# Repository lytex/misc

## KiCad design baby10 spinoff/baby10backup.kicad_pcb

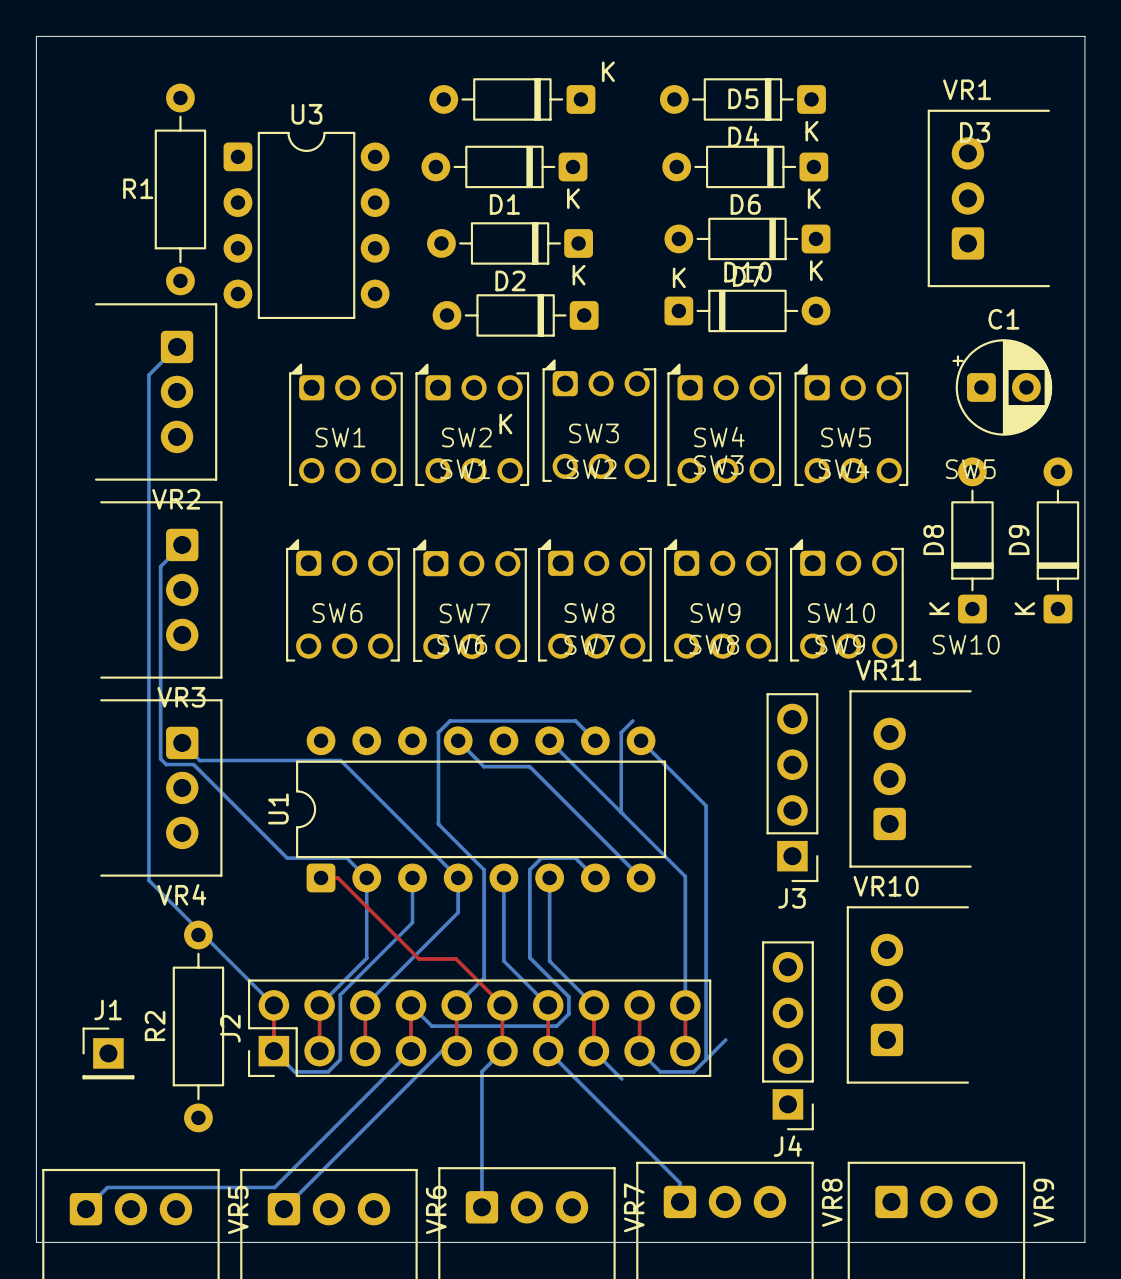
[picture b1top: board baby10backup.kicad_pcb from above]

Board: 2 copper layers, 58.2 x 67.0 mm, 40 parts (0 on the bottom side), 40 nets.

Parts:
C1: C_Polarized; CP_Radial_D5.0mm_P2.50mm
D1, D2, D3, D4, D5, D6, D7, D8, D9, D10: 1N4148; D_DO-35_SOD27_P7.62mm_Horizontal
J1: Conn_01x01; PinHeader_1x01_P2.54mm_Vertical
J2: Conn_02x10_Odd_Even; PinHeader_2x10_P2.54mm_Vertical
J3: CV; PinHeader_1x04_P2.54mm_Vertical
J4: CV Inv; PinHeader_1x04_P2.54mm_Vertical
R1: 1K; R_Axial_DIN0207_L6.3mm_D2.5mm_P10.16mm_Horizontal
R2: 100K; R_Axial_DIN0207_L6.3mm_D2.5mm_P10.16mm_Horizontal
SW1, SW2, SW3, SW4, SW5, SW6, SW7, SW8, SW9, SW10: SW_DPDT_x2_Latching; SW_DPDT_x2_Latching_2mm_pitch
U1: 4017; DIP-16_W7.62mm
U3: ICM7555xP; DIP-8_W7.62mm
VR1, VR2, VR3, VR4, VR5, VR6, VR7, VR8, VR9, VR10, VR11: 500K; Potentiometer_Alps_RK097_Single_Horizontal

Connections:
GND: C1.2, R2.1, U1.8 (VSS), U1.13 (CKEN), U3.1 (GND)
unnamed: D1.2 (A), VR2.2, VR2.3
unnamed: D1.1 (K), SW1.2 (B), SW10.5 (B)
unnamed: D2.2 (A), VR3.2, VR3.3
unnamed: D2.1 (K), SW2.2 (B), SW9.5 (B)
unnamed: D3.2 (A), VR4.2, VR4.3
unnamed: D3.1 (K), SW3.2 (B), SW8.5 (B)
unnamed: D4.2 (A), VR5.2, VR5.3
unnamed: D4.1 (K), SW4.2 (B), SW7.5 (B)
unnamed: D5.2 (A), VR6.2, VR6.3
unnamed: D5.1 (K), SW5.2 (B), SW6.5 (B)
unnamed: D6.2 (A), VR7.2, VR7.3
unnamed: D6.1 (K), SW5.5 (B), SW6.2 (B)
unnamed: D7.2 (A), VR8.2, VR8.3
unnamed: D7.1 (K), SW4.5 (B), SW7.2 (B)
unnamed: D8.2 (A), VR9.2, VR9.3
unnamed: D8.1 (K), SW3.5 (B), SW8.2 (B)
unnamed: D9.2 (A), VR10.2, VR10.3
unnamed: D9.1 (K), SW2.5 (B), SW9.2 (B)
unnamed: D10.2 (A), VR11.2, VR11.3
unnamed: D10.1 (K), SW1.5 (B), SW10.2 (B)
unnamed: J1.1, R2.2, U1.15 (Reset)
unnamed: J2.1, J2.2, U1.3 (Q0), VR2.1
unnamed: J2.3, J2.4, U1.2 (Q1), VR3.1
unnamed: J2.5, J2.6, U1.4 (Q2), VR4.1
unnamed: J2.7, J2.8, U1.7 (Q3), VR5.1
unnamed: J2.9, J2.10, U1.10 (Q4), VR6.1
unnamed: J2.11, J2.12, U1.1 (Q5), VR7.1
unnamed: J2.13, J2.14, U1.5 (Q6), VR8.1
unnamed: J2.15, J2.16, U1.6 (Q7), VR9.1
unnamed: J2.17, J2.18, U1.9 (Q8), VR10.1
unnamed: J2.19, J2.20, U1.11 (Q9), VR11.1
unnamed: J3.1, J3.2, J3.3, J3.4, SW1.1 (A), SW2.1 (A), SW3.1 (A), SW4.1 (A), SW5.1 (A), SW6.1 (A), SW7.1 (A), SW8.1 (A), SW9.1 (A), SW10.1 (A)
unnamed: J4.1, J4.2, J4.3, J4.4, SW10.4 (A)
unnamed: SW1.4 (A), SW2.4 (A), SW3.4 (A), SW4.4 (A), SW5.4 (A), SW6.4 (A), SW7.4 (A), SW8.4 (A), SW9.4 (A)
unnamed: U1.14 (CLK), U3.3 (Q)
unnamed: R1.2, U3.7 (DIS), VR1.2, VR1.3
unnamed: R1.1, U3.6 (THR)
unnamed: C1.1, U3.2 (TR)
VCC: U1.16 (VDD), U3.4 (R), U3.8 (VCC), VR1.1

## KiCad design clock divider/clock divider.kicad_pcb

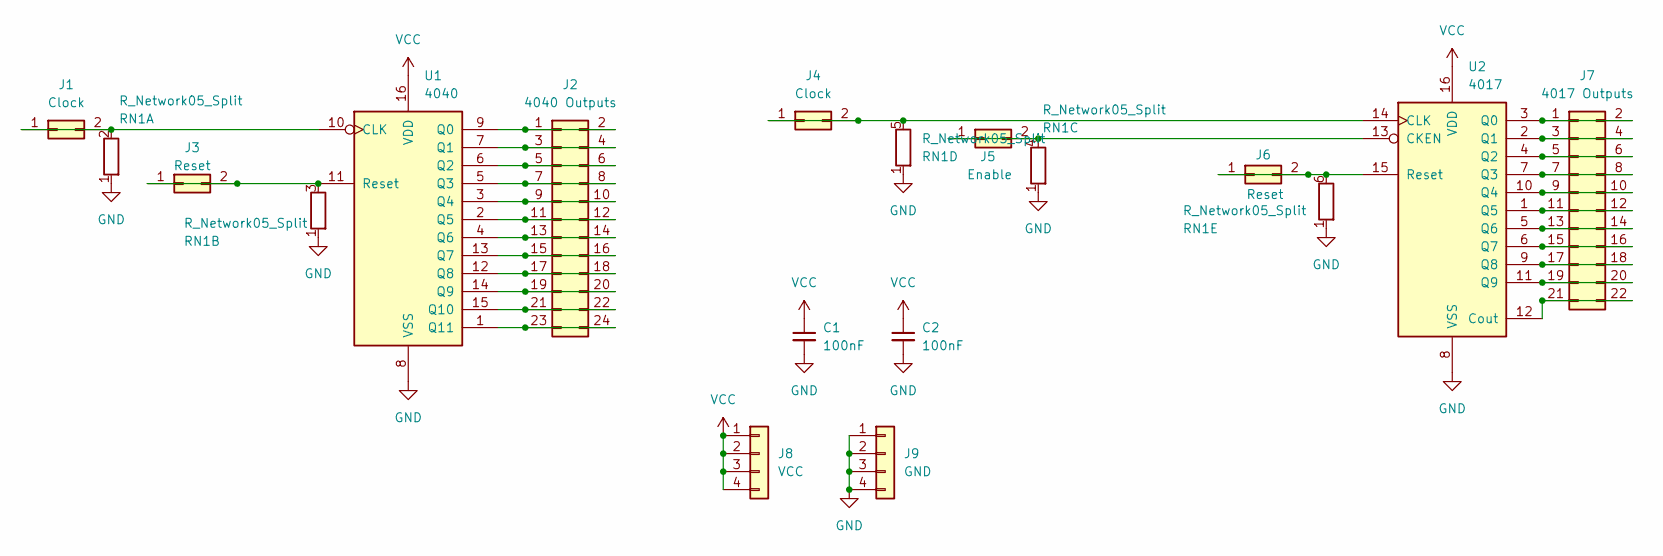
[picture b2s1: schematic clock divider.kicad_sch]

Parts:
C1, C2: 100nF; C_Disc_D3.0mm_W1.6mm_P2.50mm
J1, J4: Clock; PinHeader_2x01_P2.54mm_Vertical
J2: 4040 Outputs; PinHeader_2x12_P2.54mm_Vertical
J3, J6: Reset; PinHeader_2x01_P2.54mm_Vertical
J5: Enable; PinHeader_2x01_P2.54mm_Vertical
J7: 4017 Outputs; PinHeader_2x11_P2.54mm_Vertical
J8: VCC; PinHeader_1x04_P2.54mm_Vertical
J9: GND; PinHeader_1x04_P2.54mm_Vertical
RN1: R_Network05_Split; R_Array_SIP6
U1: 4040; DIP-16_W7.62mm
U2: 4017; DIP-16_W7.62mm

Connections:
GND: C1.2, C2.2, J9.1, J9.2, J9.3, J9.4, RN1.1 (R1), U1.8 (VSS), U2.8 (VSS)
unnamed: J1.1, J1.2, RN1.2 (R1.2), U1.10 (CLK)
unnamed: J2.1, J2.2, U1.9 (Q0)
unnamed: J2.3, J2.4, U1.7 (Q1)
unnamed: J2.5, J2.6, U1.6 (Q2)
unnamed: J2.7, J2.8, U1.5 (Q3)
unnamed: J2.9, J2.10, U1.3 (Q4)
unnamed: J2.11, J2.12, U1.2 (Q5)
unnamed: J2.13, J2.14, U1.4 (Q6)
unnamed: J2.15, J2.16, U1.13 (Q7)
unnamed: J2.17, J2.18, U1.12 (Q8)
unnamed: J2.19, J2.20, U1.14 (Q9)
unnamed: J2.21, J2.22, U1.15 (Q10)
unnamed: J2.23, J2.24, U1.1 (Q11)
unnamed: J3.1, J3.2, RN1.3 (R2.2), U1.11 (Reset)
unnamed: J4.1, J4.2, RN1.5 (R4.2), U2.14 (CLK)
unnamed: J5.1, J5.2, RN1.4 (R3.2), U2.13 (CKEN)
unnamed: J6.1, J6.2, RN1.6 (R5.2), U2.15 (Reset)
unnamed: J7.1, J7.2, U2.3 (Q0)
unnamed: J7.3, J7.4, U2.2 (Q1)
unnamed: J7.5, J7.6, U2.4 (Q2)
unnamed: J7.7, J7.8, U2.7 (Q3)
unnamed: J7.9, J7.10, U2.10 (Q4)
unnamed: J7.11, J7.12, U2.1 (Q5)
unnamed: J7.13, J7.14, U2.5 (Q6)
unnamed: J7.15, J7.16, U2.6 (Q7)
unnamed: J7.17, J7.18, U2.9 (Q8)
unnamed: J7.19, J7.20, U2.11 (Q9)
unnamed: J7.21, J7.22, U2.12 (Cout)
VCC: C1.1, C2.1, J8.1, J8.2, J8.3, J8.4, U1.16 (VDD), U2.16 (VDD)

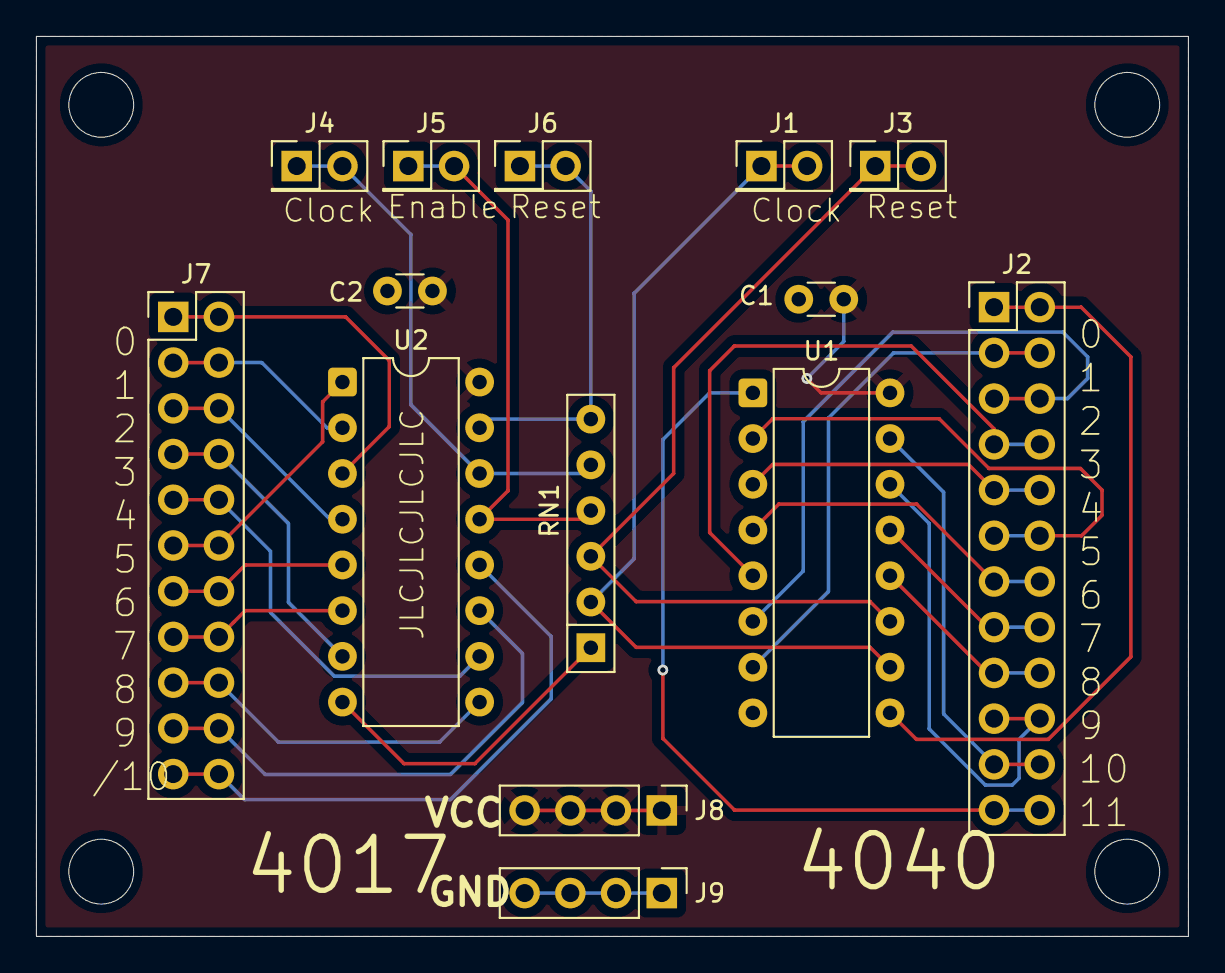
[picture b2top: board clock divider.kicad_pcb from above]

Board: 2 copper layers, 64.0 x 50.0 mm, 14 parts (0 on the bottom side), 30 nets.
